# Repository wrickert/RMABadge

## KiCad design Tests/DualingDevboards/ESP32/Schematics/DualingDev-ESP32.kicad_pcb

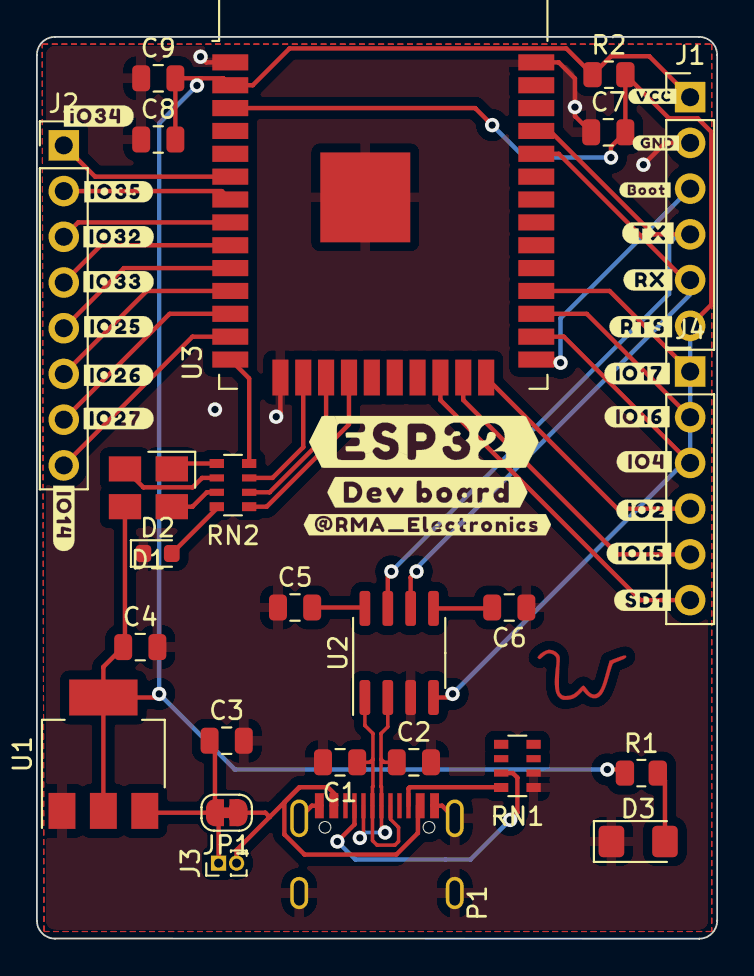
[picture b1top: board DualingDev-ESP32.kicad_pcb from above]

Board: 2 copper layers, 37.8 x 50.1 mm, 26 parts (0 on the bottom side), 37 nets.

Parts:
C1, C2: 20pF; C_0805_2012Metric
C3, C4: 1uF; C_0805_2012Metric
C5, C6, C7, C9: 100nF; C_0805_2012Metric
C8: 10uF; C_0805_2012Metric
D1: LED_BGRA; EKINGLUX-E6
D2: LED; LED_0603_1608Metric
D3: POWER; LED_1206_3216Metric_Pad1.42x1.75mm_HandSolder
J1: Program; PinHeader_1x06_P2.54mm_Vertical
J2: Conn_01x08; PinHeader_1x08_P2.54mm_Vertical
J3: Conn_01x02; PinHeader_1x02_P1.00mm_Vertical
J4: Conn_01x06; PinHeader_1x06_P2.54mm_Vertical
JP1: Jumper_NC_Small; SolderJumper-2_P1.3mm_Bridged_RoundedPad1.0x1.5mm
P1: USB_C_Plug_corrected; USB_C_Receptical-Jing
R1: R; R_0805_2012Metric
R2: 10k; R_0805_2012Metric
RN1: 5.1k; R_Array_Convex_4x0603
RN2: 270; R_Array_Convex_4x0603
Ref**: Val**; W
U1: TLV1117-33; SOT-223-3_TabPin2
U2: CH330N; SOIC-8_3.9x4.9mm_P1.27mm
U3: ESP32-WROOM-32

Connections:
1: J2.1, U3.6 (IO34)
2: J2.2, U3.7 (IO35)
3: J2.3, U3.8 (IO32)
4: J2.4, U3.9 (IO33)
5: J2.5, U3.10 (IO25)
6: J2.6, U3.11 (IO26)
7: J2.7, U3.12 (IO27)
8: J2.8, U3.13 (IO14)
/D+: C1.1, P1.A6 (D+), P1.B6 (D+), U2.1 (UD+)
/D-: C2.1, P1.A7 (D-), P1.B7 (D-), U2.2 (UD-)
A: J4.1, U3.28 (IO17)
Attention: RN2.1 (R1.1), U3.18 (SWP/SD3)
B: J4.2, U3.27 (IO16)
Blue: RN2.4 (R4.1), U3.14 (IO12)
Boot: J1.3, U3.25 (IO0)
C: J4.3, U3.26 (IO4)
D: J4.4, U3.24 (IO2)
E: J4.5, U3.23 (IO15)
F: J4.6, U3.22 (SDI/SD1)
GND: C1.2, C2.2, C3.2, C4.2, C5.1, C6.1, C7.1, C8.1, C9.1, D2.1 (K), D3.1 (K), J1.2, P1.A1 (GND), P1.A12 (GND), P1.B1 (GND), P1.B12 (GND), P1.S1 (SHIELD), RN1.1 (R1.1), RN1.2 (R2.1), U1.1 (GND), U2.3 (GND), U3.1 (GND), U3.15 (GND), U3.38 (GND), U3.39 (GND)
Green: RN2.3 (R3.1), U3.16 (IO13)
unnamed: C3.1, J3.1, JP1.2, U1.3 (VI)
unnamed: C5.2, U2.8 (V3)
unnamed: C6.2, U2.5 (VCC)
unnamed: D1.1 (BK), RN2.5 (R4.2)
unnamed: D1.2 (GK), RN2.6 (R3.2)
unnamed: D1.3 (RK), RN2.7 (R2.2)
unnamed: D2.2 (A), RN2.8 (R1.2)
unnamed: D3.2 (A), R1.2
unnamed: P1.A5 (CC), RN1.7 (R2.2)
unnamed: P1.B5 (VCONN), RN1.8 (R1.2)
RTS: C7.2, J1.6, R2.2, U2.4 (~RTS), U3.3 (EN)
RX: J1.5, U2.6 (TXD), U3.34 (RXD0/IO3)
Red: RN2.2 (R2.1), U3.17 (SHD/SD2)
TX: J1.4, U2.7 (RXD), U3.35 (TXD0/IO1)
VBUS: J3.2, JP1.1, P1.A4 (VBUS), P1.A9 (VBUS), P1.B4 (VBUS), P1.B9 (VBUS)
VCC: C4.1, C8.2, C9.2, D1.4 (A), J1.1, R1.1, R2.1, U1.2 (VO), U3.2 (VDD)

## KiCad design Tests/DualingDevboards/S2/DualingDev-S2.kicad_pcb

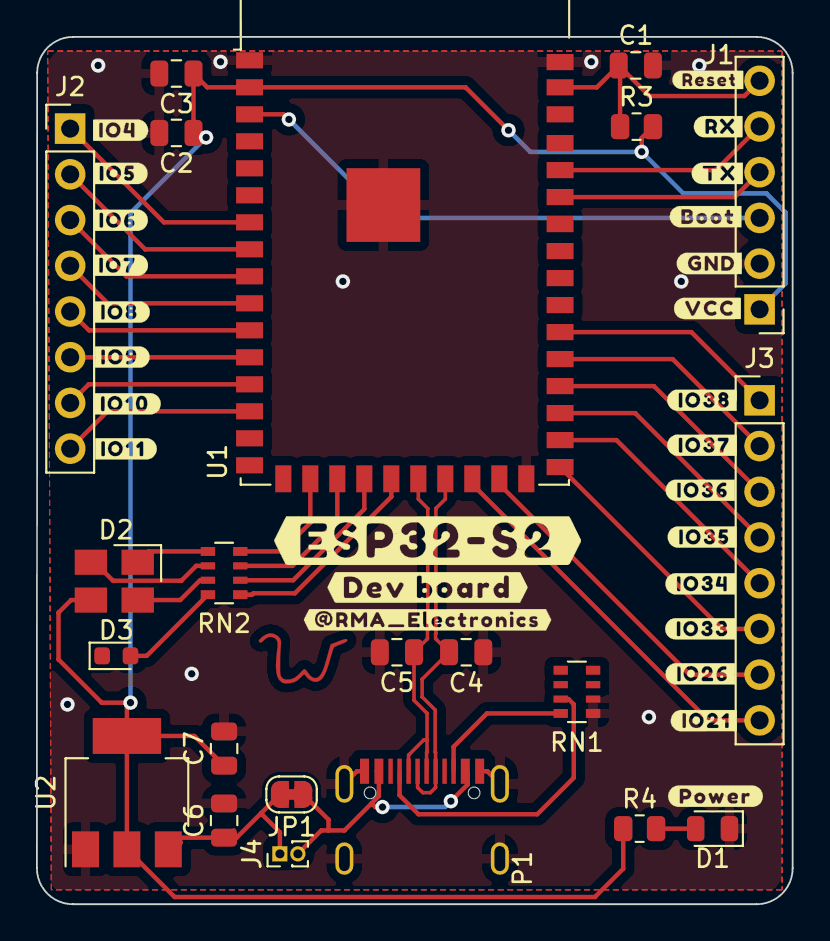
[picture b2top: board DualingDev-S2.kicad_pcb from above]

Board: 2 copper layers, 42.0 x 48.2 mm, 23 parts (0 on the bottom side), 37 nets.

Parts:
C1, C2: 100nF; C_0805_2012Metric
C3: 22uF; C_0805_2012Metric
C4, C5: 20pF; C_0805_2012Metric
C6, C7: 1uF; C_0805_2012Metric
D1: POWER; LED_0805_2012Metric
D2: LED_BGRA; EKINGLUX-E6
D3: LED; LED_0603_1608Metric
J1: Program; PinHeader_1x06_P2.54mm_Vertical
J2, J3: Conn_01x08; PinHeader_1x08_P2.54mm_Vertical
J4: Conn_01x02; PinHeader_1x02_P1.00mm_Vertical
JP1: Jumper_NC_Small; SolderJumper-2_P1.3mm_Bridged_RoundedPad1.0x1.5mm
P1: USB_C_Plug_corrected; USB_C_Receptical-Jing
R3: 1k; R_0805_2012Metric
R4: R; R_0805_2012Metric
RN1: 5.1k; R_Array_Convex_4x0603
RN2: 270; R_Array_Convex_4x0603
Ref**: Val**; W
U1: ESP32-S2-WROVER
U2: TLV1117-33; SOT-223-3_TabPin2

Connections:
/D+: C4.1, P1.A6 (D+), P1.B6 (D+), U1.23 (USB_D+)
/D-: C5.1, P1.A7 (D-), P1.B7 (D-), U1.22 (USB_D-)
Attention: RN2.1 (R1.1), U1.21 (IO18)
Blue: RN2.4 (R4.1), U1.18 (IO15)
Boot: J1.3, U1.3 (IO00)
GND: C1.2, C2.2, C3.2, C4.2, C5.2, C6.2, C7.2, D1.1 (K), J1.2, P1.A1 (GND), P1.A12 (GND), P1.B1 (GND), P1.B12 (GND), P1.S1 (SHIELD), RN1.1 (R1.1), RN1.2 (R2.1), U1.1 (GND), U1.26 (GND), U1.42 (GND), U1.43 (GND), U2.1 (GND)
Green: RN2.3 (R3.1), U1.19 (IO16)
unnamed: C6.1, J4.1, JP1.2, U2.3 (VI)
unnamed: D1.2 (A), R4.2
unnamed: D2.1 (BK), RN2.5 (R4.2)
unnamed: D2.2 (GK), RN2.6 (R3.2)
unnamed: D2.3 (RK), RN2.7 (R2.2)
unnamed: D3.2 (A), RN2.8 (R1.2)
unnamed: J2.1, U1.7 (IO04)
unnamed: J2.2, U1.8 (IO05)
unnamed: J2.3, U1.9 (IO06)
unnamed: J2.4, U1.10 (IO07)
unnamed: J2.5, U1.11 (IO08)
unnamed: J2.6, U1.12 (IO09)
unnamed: J2.7, U1.13 (IO10)
unnamed: J2.8, U1.14 (IO11)
unnamed: J3.1, U1.32 (IO38)
unnamed: J3.2, U1.31 (IO37)
unnamed: J3.3, U1.30 (IO36)
unnamed: J3.4, U1.29 (IO35)
unnamed: J3.5, U1.28 (IO34)
unnamed: J3.6, U1.27 (IO33)
unnamed: J3.7, U1.25 (IO26)
unnamed: J3.8, U1.24 (IO21)
unnamed: P1.A5 (CC), RN1.7 (R2.2)
unnamed: P1.B5 (VCONN), RN1.8 (R1.2)
RX: J1.5, U1.38 (RXD0)
Red: RN2.2 (R2.1), U1.20 (IO17)
Reset: C1.1, J1.6, R3.1, U1.41 (EN)
TX: J1.4, U1.37 (TXD0)
VBUS: J4.2, JP1.1, P1.A4 (VBUS), P1.A9 (VBUS), P1.B4 (VBUS), P1.B9 (VBUS)
VCC: C2.1, C3.1, C7.1, D2.4 (A), J1.1, R3.2, R4.1, U1.2 (3V3), U2.2 (VO)

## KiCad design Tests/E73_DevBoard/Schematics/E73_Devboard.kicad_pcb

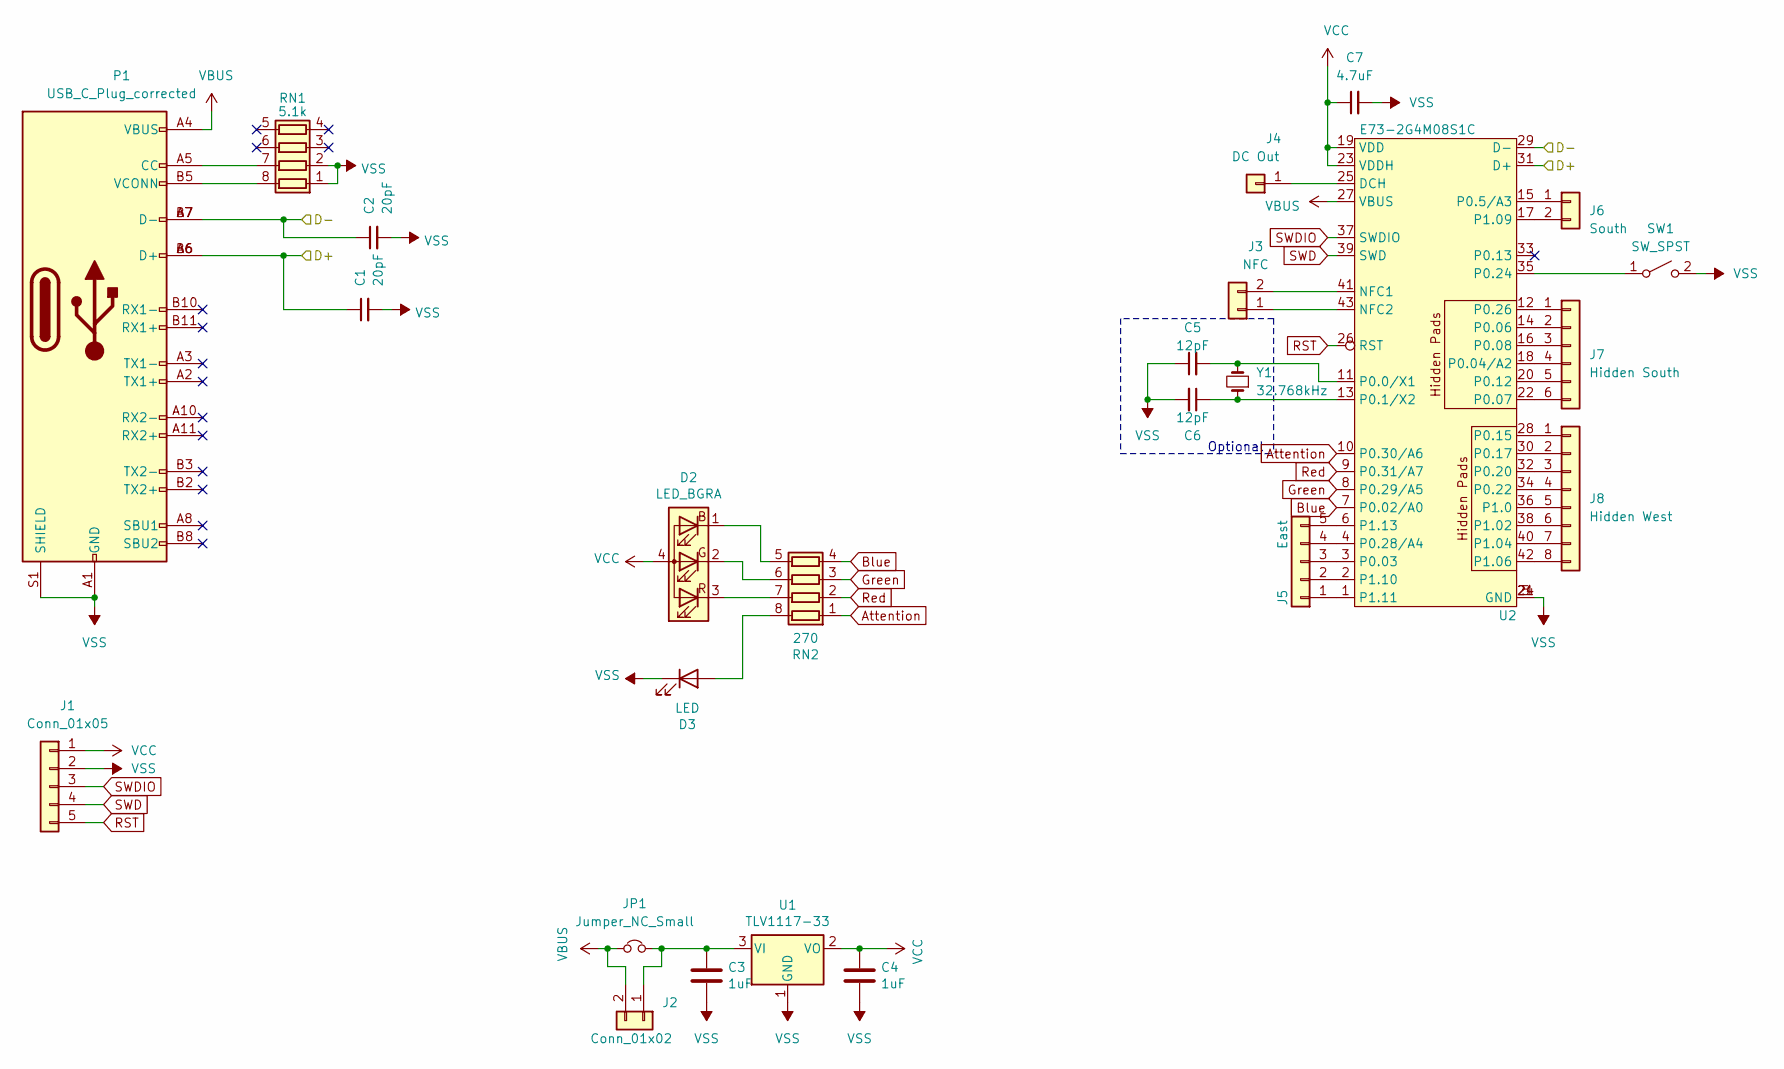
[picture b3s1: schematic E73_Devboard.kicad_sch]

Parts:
C1, C2: 20pF; C_0805_2012Metric
C3, C4: 1uF; C_0805_2012Metric
C5, C6: 12pF; C_0805_2012Metric
C7: 4.7uF; C_0805_2012Metric
D2: LED_BGRA; EKINGLUX-E6
D3: LED; LED_0603_1608Metric
J1: Conn_01x05; PinHeader_1x05_P2.54mm_Vertical
J2: Conn_01x02; PinHeader_1x02_P1.00mm_Vertical
J3: NFC; PinHeader_1x02_P2.54mm_Vertical
J4: DC Out; PinHeader_1x01_P2.54mm_Vertical
J5: East; PinHeader_1x05_P2.54mm_Vertical
J6: South; PinHeader_1x02_P2.54mm_Vertical
J7: Hidden South; PinHeader_1x06_P2.54mm_Vertical
J8: Hidden West; PinHeader_1x08_P1.00mm_Vertical_SMD_Pin1Left
JP1: Jumper_NC_Small; SolderJumper-2_P1.3mm_Bridged_RoundedPad1.0x1.5mm
P1: USB_C_Plug_corrected; USB_C_Receptical-Jing
RN1: 5.1k; R_Array_Convex_4x0603
RN2: 270; R_Array_Convex_4x0603
SW1: SW_SPST; 1TS002E-2500-2500-CT-HYP-Button
U1: TLV1117-33; SOT-223-3_TabPin2
U2: E73-2G4M08S1C
Y1: 32.768kHz; Crystal_SMD_3215-2Pin_3.2x1.5mm

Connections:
/D+: C1.1, P1.A6 (D+), P1.B6 (D+), U2.31 (D+)
/D-: C2.1, P1.A7 (D-), P1.B7 (D-), U2.29 (D-)
Attention: RN2.1 (R1.1), U2.10 (P0.30/A6)
Blue: RN2.4 (R4.1), U2.7 (P0.02/A0)
Green: RN2.3 (R3.1), U2.8 (P0.29/A5)
unnamed: C3.1, J2.1, JP1.2, U1.3 (VI)
unnamed: C5.2, U2.11 (P0.0/X1), Y1.2
unnamed: C6.1, U2.13 (P0.1/X2), Y1.1
unnamed: D2.1 (BK), RN2.5 (R4.2)
unnamed: D2.2 (GK), RN2.6 (R3.2)
unnamed: D2.3 (RK), RN2.7 (R2.2)
unnamed: D3.2 (A), RN2.8 (R1.2)
unnamed: J3.1, U2.43 (NFC2)
unnamed: J3.2, U2.41 (NFC1)
unnamed: J4.1, U2.25 (DCH)
unnamed: J5.1, U2.1 (P1.11)
unnamed: J5.2, U2.2 (P1.10)
unnamed: J5.3, U2.3 (P0.03)
unnamed: J5.4, U2.4 (P0.28/A4)
unnamed: J5.5, U2.6 (P1.13)
unnamed: J6.1, U2.15 (P0.5/A3)
unnamed: J6.2, U2.17 (P1.09)
unnamed: J7.1, U2.12 (P0.26)
unnamed: J7.2, U2.14 (P0.06)
unnamed: J7.3, U2.16 (P0.08)
unnamed: J7.4, U2.18 (P0.04/A2)
unnamed: J7.5, U2.20 (P0.12)
unnamed: J7.6, U2.22 (P0.07)
unnamed: J8.1, U2.28 (P0.15)
unnamed: J8.2, U2.30 (P0.17)
unnamed: J8.3, U2.32 (P0.20)
unnamed: J8.4, U2.34 (P0.22)
unnamed: J8.5, U2.36 (P1.0)
unnamed: J8.6, U2.38 (P1.02)
unnamed: J8.7, U2.40 (P1.04)
unnamed: J8.8, U2.42 (P1.06)
unnamed: P1.A5 (CC), RN1.7 (R2.2)
unnamed: P1.B5 (VCONN), RN1.8 (R1.2)
unnamed: SW1.1 (A), U2.35 (P0.24)
RST: J1.5, U2.26 (RST)
Red: RN2.2 (R2.1), U2.9 (P0.31/A7)
SWD: J1.4, U2.39 (SWD)
SWDIO: J1.3, U2.37 (SWDIO)
VBUS: J2.2, JP1.1, P1.A4 (VBUS), P1.A9 (VBUS), P1.B4 (VBUS), P1.B9 (VBUS), U2.27 (VBUS)
VCC: C4.1, C7.1, D2.4 (A), J1.1, U1.2 (VO), U2.19 (VDD), U2.23 (VDDH)
VSS: C1.2, C2.2, C3.2, C4.2, C5.1, C6.2, C7.2, D3.1 (K), J1.2, P1.A1 (GND), P1.A12 (GND), P1.B1 (GND), P1.B12 (GND), P1.S1 (SHIELD), RN1.1 (R1.1), RN1.2 (R2.1), SW1.2 (B), U1.1 (GND), U2.5 (GND), U2.21 (GND), U2.24 (GND)

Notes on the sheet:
Optional

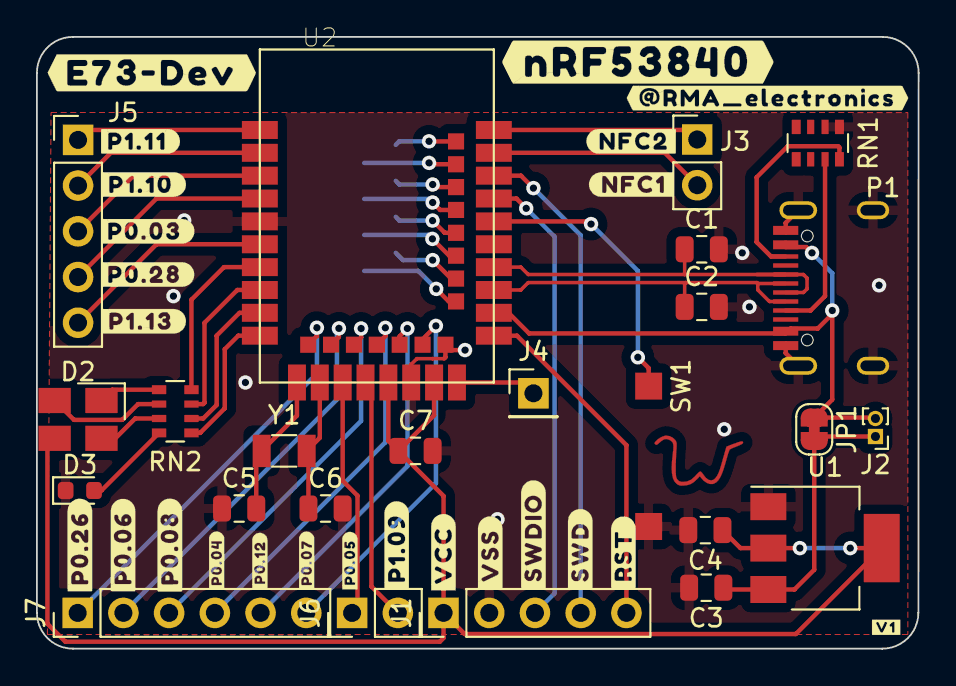
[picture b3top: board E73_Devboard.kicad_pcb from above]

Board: 2 copper layers, 49.0 x 34.0 mm, 26 parts (1 on the bottom side), 46 nets.

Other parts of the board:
Ref**: Val**; W

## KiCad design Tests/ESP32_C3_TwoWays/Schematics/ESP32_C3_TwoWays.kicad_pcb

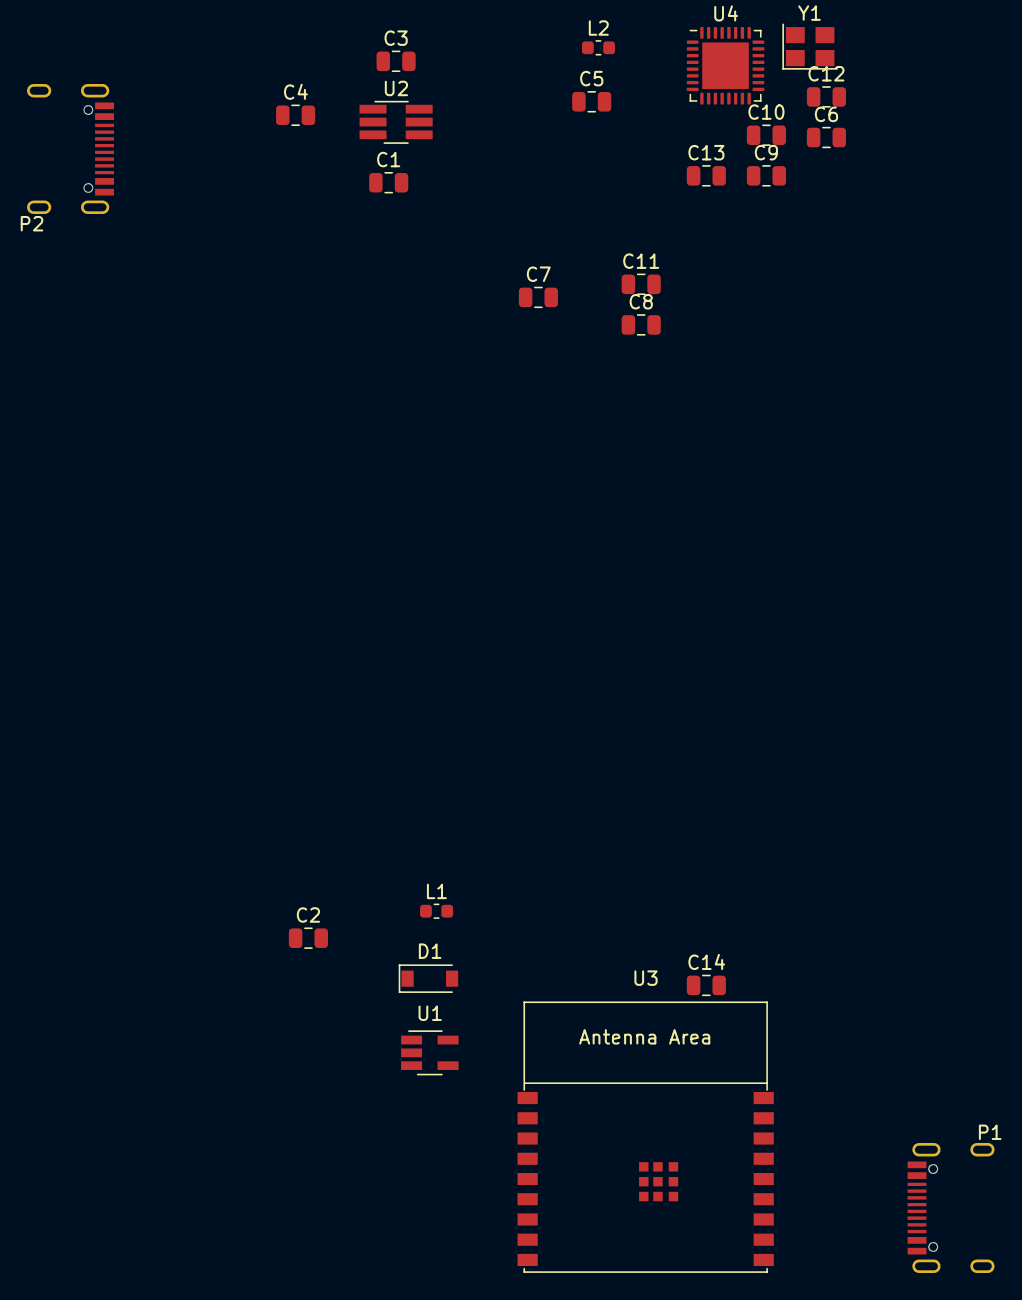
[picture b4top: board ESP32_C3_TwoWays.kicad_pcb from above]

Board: 2 copper layers, 24 parts (0 on the bottom side), 15 nets, no tracks yet.

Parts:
C1, C4, C6: 10uF; C_0805_2012Metric
C2: 47uF; C_0805_2012Metric
C3: 2.2uF; C_0805_2012Metric
C5, C8, C14: C_Small; C_0805_2012Metric
C7: 1uF; C_0805_2012Metric
C9, C10, C12, C13: 100nF; C_0805_2012Metric
C11: 10nF; C_0805_2012Metric
D1: Schottky; D_SOD-123
L1: L_Small; L_0603_1608Metric
L2: 2nH; L_0603_1608Metric
P1, P2: USB_C_Plug; USB_C_Receptical-Jing
U1: RN5RK331A; SOT-23-5_HandSoldering
U2: XDS_TX4310B; TSOT-23-6_HandSoldering
U3: ESP32-C3-WROOM-02
U4: ESP32-C3; QFN-32-1EP_5x5mm_P0.5mm_EP3.45x3.45mm
Y1: 40MHz; Crystal_SMD_3225-4Pin_3.2x2.5mm

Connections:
+5V: L1.1, P1.A4 (VBUS), P1.A9 (VBUS), P1.B4 (VBUS), P1.B9 (VBUS)
D1+: P2.A6 (D+), U4.26 (GPIO19/USB_D+)
D1-: P2.A7 (D-), U4.25 (GPIO18/USB_D-)
D2+: P1.A6 (D+), U3.14 (GPIO19/USB_D+)
D2-: P1.A7 (D-), U3.13 (GPIO18/USB_D-)
unnamed: C3.1, U2.6 (C+)
unnamed: C3.2, U2.4 (C-)
unnamed: C5.2, U4.30 (XTAL_P), Y1.1
unnamed: C8.2, U4.29 (XTAL_N), Y1.3
unnamed: C12.1, L2.2, U4.2 (VDD3P3), U4.3 (VDD3P3)
unnamed: D1.2 (A), L1.2, U1.5 (Lx)
VAA: C2.2, C14.1, D1.1 (K), U1.1 (En), U1.2 (Vout), U3.1 (3V3)
VBUS: C1.1, P2.A4 (VBUS), P2.A9 (VBUS), P2.B4 (VBUS), P2.B9 (VBUS), U2.3 (En), U2.5 (VDD)
VCC: C4.1, C6.1, C7.1, C9.1, C10.1, C11.1, C13.1, L2.1, U2.1 (Vout), U4.11 (VDD3P3_RTC), U4.17 (VDD3P3_CPU), U4.31 (VDDA), U4.32 (VDDA)
VSS: C1.2, C2.1, C4.2, C5.1, C6.2, C7.2, C8.1, C9.2, C10.2, C11.2, C12.2, C13.2, C14.2, P1.A1 (GND), P1.A12 (GND), P1.B1 (GND), P1.B12 (GND), P1.S1 (SHIELD), P2.A1 (GND), P2.A12 (GND), P2.B1 (GND), P2.B12 (GND), P2.S1 (SHIELD), U1.4 (GND), U2.2 (GND), U3.9 (GND), U3.19 (GND), U4.33 (GND), Y1.2, Y1.4

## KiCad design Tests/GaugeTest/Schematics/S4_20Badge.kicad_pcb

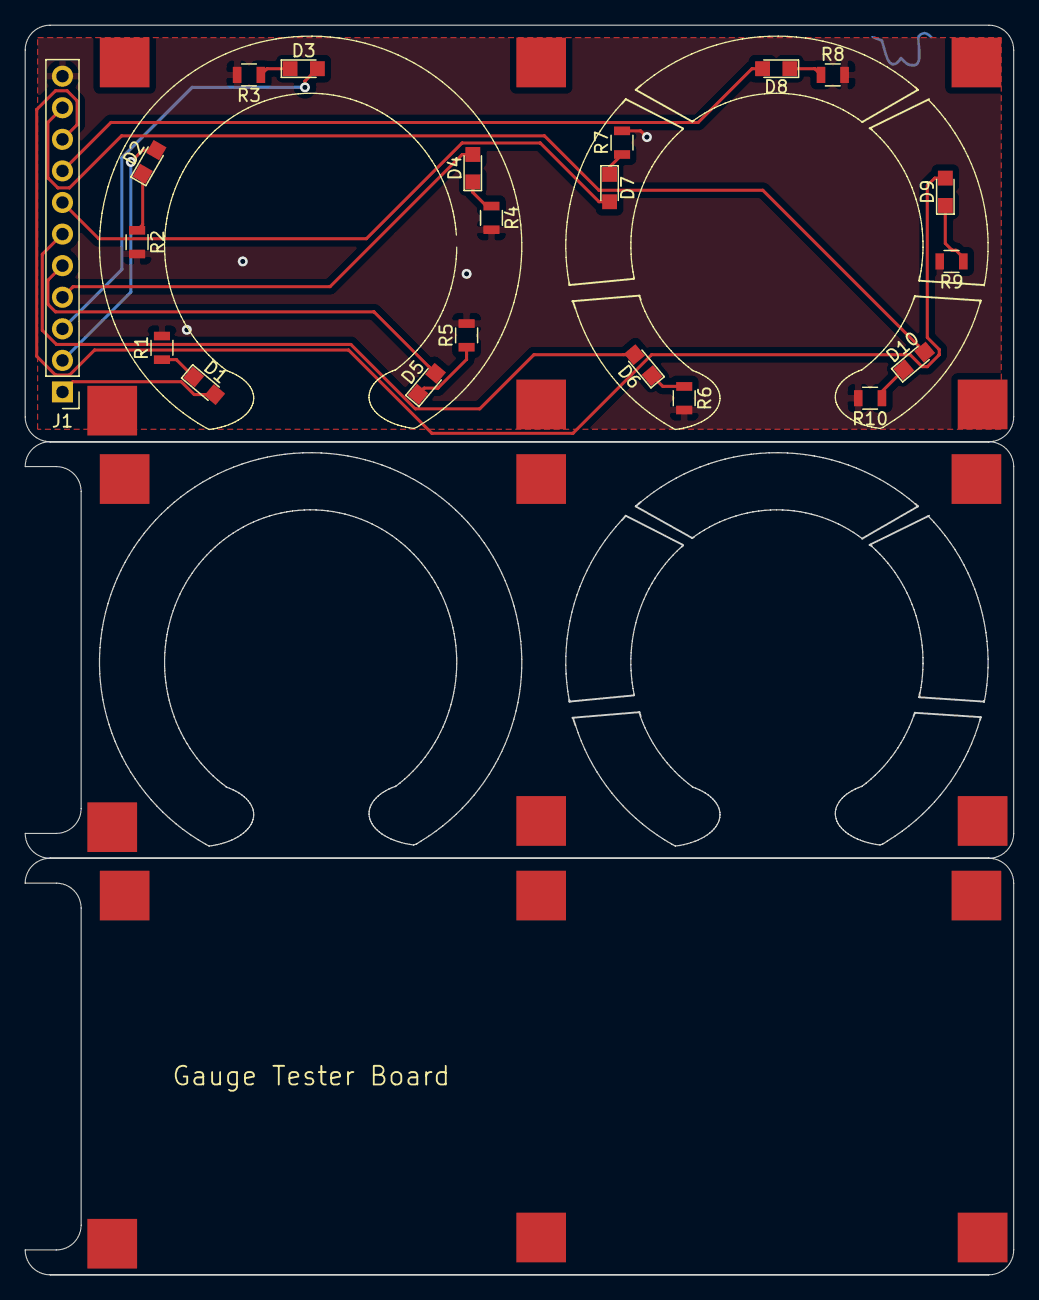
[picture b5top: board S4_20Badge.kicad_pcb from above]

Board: 2 copper layers, 79.5 x 100.5 mm, 27 parts (1 on the bottom side), 21 nets.

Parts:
D1, D2, D3, D4, D5, D6, D7, D8, D9, D10: LED; LED_0805
J1: Conn_01x11; Pin_Header_Straight_1x11_Pitch2.54mm
R1, R2, R3, R4, R5, R6, R7, R8, R9, R10: R_Small; R_0805
Ref**: Val**; W
Ref**#2: Val**; Gauge_silk
Ref**#3: Val**; Gauge_Open_Silk
Ref**#4: Val**; Gauge_Open_mask
Ref**#5, Ref**#6: Val**; Gauge

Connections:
unnamed: D1.1, R1.1
unnamed: D2.1, R2.1
unnamed: D3.1, R3.1
unnamed: D4.1, R4.1
unnamed: D5.1, R5.1
unnamed: D6.1, R6.1
unnamed: D7.1, R7.1
unnamed: D8.1, R8.1
unnamed: D9.1, R9.1
unnamed: D10.1, R10.1
VSS: J1.11, R1.2, R2.2, R3.2, R4.2, R5.2, R6.2, R7.2, R8.2, R9.2, R10.2
a: D1.2, J1.1
b: D2.2, J1.2
c: D3.2, J1.3
d: D4.2, J1.4
e: D5.2, J1.5
f: D6.2, J1.6
g: D7.2, J1.7
h: D8.2, J1.8
i: D9.2, J1.9
j: D10.2, J1.10

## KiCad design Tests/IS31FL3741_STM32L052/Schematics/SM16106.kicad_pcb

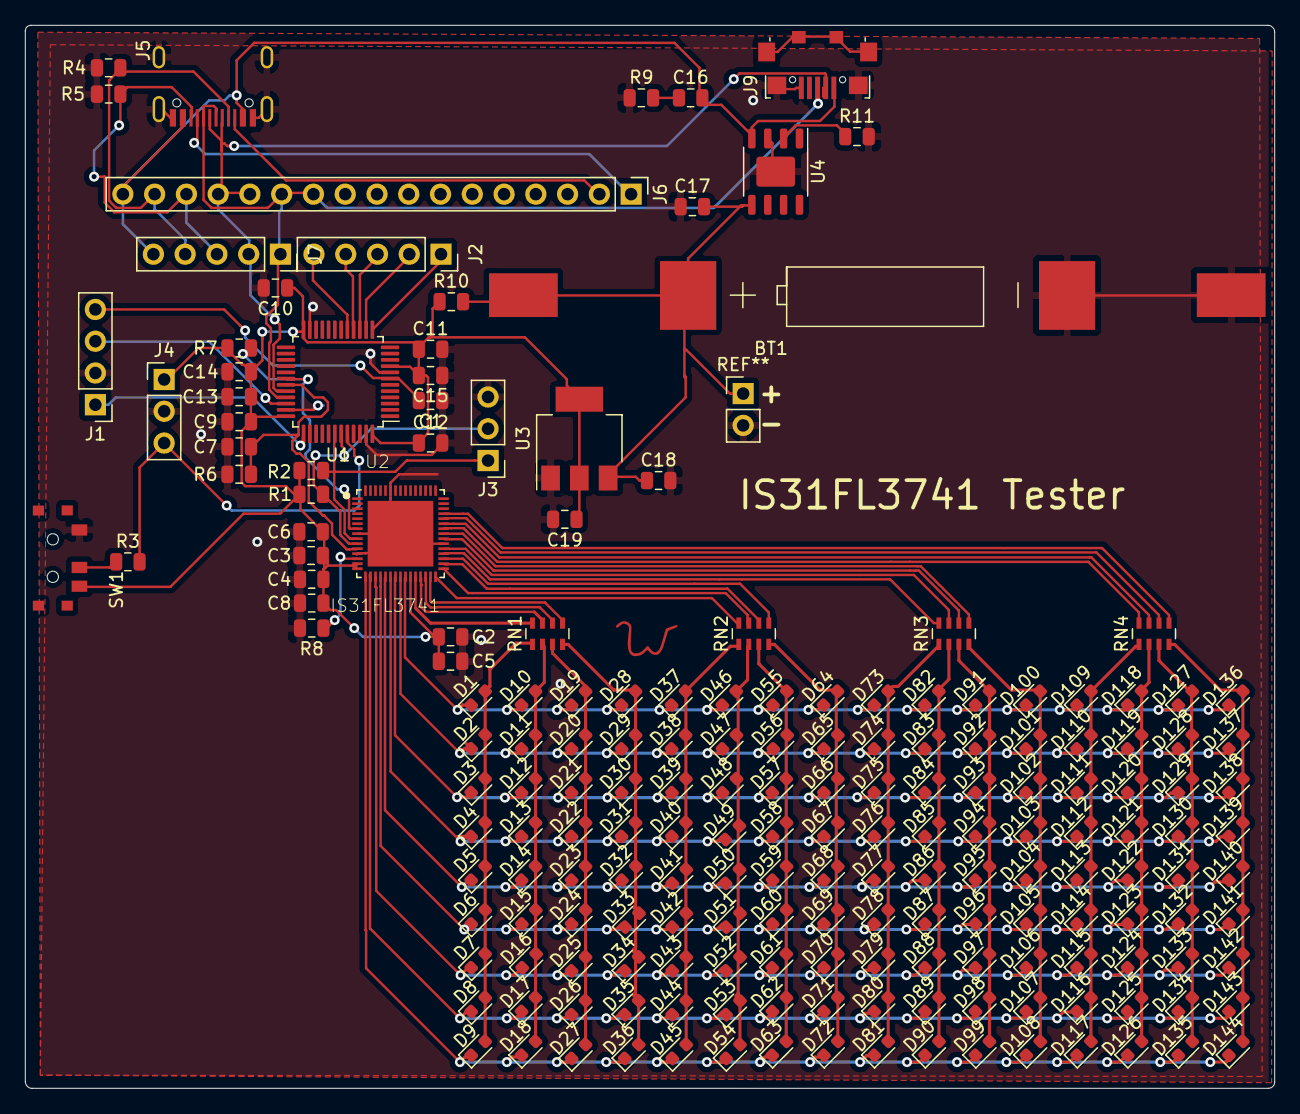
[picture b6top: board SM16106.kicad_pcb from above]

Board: 2 copper layers, 99.9 x 85.0 mm, 193 parts (0 on the bottom side), 68 nets.

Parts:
BT1: Battery_Cell; Dongguan14500
C1, C9, C10, C11, C12, C13: 100nF; C_0805_2012Metric
C2, C3, C4, C15, C18, C19: 1uF; C_0805_2012Metric
C5, C6, C7, C8: 100pF; C_0805_2012Metric
C14, C16, C17: 10uF; C_0805_2012Metric
D1, D2, D3, D4, D5, D6, D7, D8, D9, D10, D11, D12, D13, D14, D15, D16, D17, D18, D19, D20, D21, D22, D23, D24, D25, D26, D27, D28, D29, D30, D31, D32, D33, D34, D35, D36, D37, D38, D39, D40, D41, D42, D43, D44, D45, D46, D47, D48, D49, D50, D51, D52, D53, D54, D55, D56, D57, D58, D59, D60, D61, D62, D63, D64, D65, D66, D67, D68, D69, D70, D71, D72, D73, D74, D75, D76, D77, D78, D79, D80, D81, D82, D83, D84, D85, D86, D87, D88, D89, D90, D91, D92, D93, D94, D95, D96, D97, D98, D99, D100, D101, D102, D103, D104, D105, D106, D107, D108, D109, D110, D111, D112, D113, D114, D115, D116, D117, D118, D119, D120, D121, D122, D123, D124, D125, D126, D127, D128, D129, D130, D131, D132, D133, D134, D135, D136, D137, D138, D139, D140, D141, D142, D143, D144: LED; LED_0603_1608Metric
J1: Prog; PinHeader_1x04_P2.54mm_Vertical
J2: Expansion; PinSocket_1x05_P2.54mm_Vertical
J3: i2c; PinHeader_1x03_P2.54mm_Vertical
J4: Conn_01x03; PinHeader_1x03_P2.54mm_Vertical
J5: USB_C_Receptacle; USB_C_Receptical-Jing
J6: Conn_01x17; PinHeader_1x17_P2.54mm_Vertical
J7: Conn_01x05; PinSocket_1x05_P2.54mm_Vertical
J9: USB_B_Micro; USB_Micro-B_Jing
R1, R2: 2k; R_0805_2012Metric
R3, R4, R5, R6, R7, R8: 10k; R_0805_2012Metric
R9: 1.5; R_0805_2012Metric
R10: 0ohm; R_0805_2012Metric
R11: 1k; R_0805_2012Metric
RN1, RN2, RN3, RN4: R_Pack04; R_Array_Concave_4x0603
Ref**: Val**; W
SW1: SW_SPDT; SK-3296S_switch
U1: STM32L052C8Tx; LQFP-48_7x7mm_P0.5mm
U2: IS31FL3741; QFN40P700X700X75-61N
U3: TLV1117-33; SOT-223-3_TabPin2
U4: HX4056; HSOP-8-1EP_3.9x4.9mm_P1.27mm_EP2.41x3.1mm

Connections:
+5V: C16.2, J5.A4, J5.A9, J5.B4, J5.B9, J6.17, J7.5, J9.1, U4.4
/INTB: R7.1, U1.30, U2.7
/SCL: J3.1, R2.2, U1.42, U2.9
/SDA: J3.2, R1.2, U1.43, U2.10
/SDB: C7.1, R6.2, U1.31, U2.11
Boot0: J4.3, R3.2, U1.44
C1: D1.2, D2.2, D3.2, D4.2, D5.2, D6.2, D7.2, D8.2, D9.2, RN1.1
C2: D10.2, D11.2, D12.2, D13.2, D14.2, D15.2, D16.2, D17.2, D18.2, RN1.2
C3: D19.2, D20.2, D21.2, D22.2, D23.2, D24.2, D25.2, D26.2, D27.2, RN1.3
C4: D28.2, D29.2, D30.2, D31.2, D32.2, D33.2, D34.2, D35.2, D36.2, RN1.4
C5: D37.2, D38.2, D39.2, D40.2, D41.2, D42.2, D43.2, D44.2, D45.2, RN2.1
C6: D46.2, D47.2, D48.2, D49.2, D50.2, D51.2, D52.2, D53.2, D54.2, RN2.2
C7: D55.2, D56.2, D57.2, D58.2, D59.2, D60.2, D61.2, D62.2, D63.2, RN2.3
C8: D64.2, D65.2, D66.2, D67.2, D68.2, D69.2, D70.2, D71.2, D72.2, RN2.4
C9: D73.2, D74.2, D75.2, D76.2, D77.2, D78.2, D79.2, D80.2, D81.2, RN3.1
C10: D82.2, D83.2, D84.2, D85.2, D86.2, D87.2, D88.2, D89.2, D90.2, RN3.2
C11: D91.2, D92.2, D93.2, D94.2, D95.2, D96.2, D97.2, D98.2, D99.2, RN3.3
C12: D100.2, D101.2, D102.2, D103.2, D104.2, D105.2, D106.2, D107.2, D108.2, RN3.4
C13: D109.2, D110.2, D111.2, D112.2, D113.2, D114.2, D115.2, D116.2, D117.2, RN4.1
C14: D118.2, D119.2, D120.2, D121.2, D122.2, D123.2, D124.2, D125.2, D126.2, RN4.2
C15: D127.2, D128.2, D129.2, D130.2, D131.2, D132.2, D133.2, D134.2, D135.2, RN4.3
C16: D136.2, D137.2, D138.2, D139.2, D140.2, D141.2, D142.2, D143.2, D144.2, RN4.4
D+: J5.A6, J5.B6, J6.11, J6.12, J7.1, J9.3, U1.33
D-: J5.A7, J5.B7, J6.13, J6.14, J7.2, J9.2, U1.32
GND: BT1.2, C1.1, C2.2, C3.2, C4.2, C5.2, C6.2, C7.2, C8.2, C9.2, C10.2, C11.2, C12.2, C13.2, C14.2, C15.2, C17.1, C18.2, C19.2, J1.2, J3.3, J4.2, J5.A1, J5.A12, J5.B1, J5.B12, J5.S1, J9.5, J9.6, R4.1, R5.1, R6.1, R8.2, R9.1, R11.2, SW1.3, U1.8, U1.23, U1.35, U1.47, U2.8, U2.12, U2.36, U2.55, U2.61, U3.1, U4.3, U4.9
unnamed: C16.1, R9.2
unnamed: J5.A5, J6.16, J7.4, R4.2
unnamed: J5.A8, J6.2
unnamed: J5.B5, J6.15, J7.3, R5.2
unnamed: J5.B8, J6.1
unnamed: R3.1, SW1.2
unnamed: R8.1, U2.13
unnamed: R11.1, U4.2
unnamed: RN1.5, U2.29
unnamed: RN1.6, U2.28
unnamed: RN1.7, U2.27
unnamed: RN1.8, U2.26
unnamed: RN2.5, U2.33
unnamed: RN2.6, U2.32
unnamed: RN2.7, U2.31
unnamed: RN2.8, U2.30
unnamed: RN3.5, U2.38
unnamed: RN3.6, U2.37
unnamed: RN3.7, U2.35
unnamed: RN3.8, U2.34
unnamed: RN4.5, U2.42
unnamed: RN4.6, U2.41
unnamed: RN4.7, U2.40
unnamed: RN4.8, U2.39
PA3: J2.1, U1.13
PA4: J2.2, U1.14
PA5: J2.3, U1.15
PA6: J2.4, U1.16
PA7: J2.5, U1.17
R1: D1.1, D10.1, D19.1, D28.1, D37.1, D46.1, D55.1, D64.1, D73.1, D82.1, D91.1, D100.1, D109.1, D118.1, D127.1, D136.1, U2.24
R2: D2.1, D11.1, D20.1, D29.1, D38.1, D47.1, D56.1, D65.1, D74.1, D83.1, D92.1, D101.1, D110.1, D119.1, D128.1, D137.1, U2.23
R3: D3.1, D12.1, D21.1, D30.1, D39.1, D48.1, D57.1, D66.1, D75.1, D84.1, D93.1, D102.1, D111.1, D120.1, D129.1, D138.1, U2.22
R4: D4.1, D13.1, D22.1, D31.1, D40.1, D49.1, D58.1, D67.1, D76.1, D85.1, D94.1, D103.1, D112.1, D121.1, D130.1, D139.1, U2.21
R5: D5.1, D14.1, D23.1, D32.1, D41.1, D50.1, D59.1, D68.1, D77.1, D86.1, D95.1, D104.1, D113.1, D122.1, D131.1, D140.1, U2.20
R6: D6.1, D15.1, D24.1, D33.1, D42.1, D51.1, D60.1, D69.1, D78.1, D87.1, D96.1, D105.1, D114.1, D123.1, D132.1, D141.1, U2.19
R7: D7.1, D16.1, D25.1, D34.1, D43.1, D52.1, D61.1, D70.1, D79.1, D88.1, D97.1, D106.1, D115.1, D124.1, D133.1, D142.1, U2.18
R8: D8.1, D17.1, D26.1, D35.1, D44.1, D53.1, D62.1, D71.1, D80.1, D89.1, D98.1, D107.1, D116.1, D125.1, D134.1, D143.1, U2.17
R9: D9.1, D18.1, D27.1, D36.1, D45.1, D54.1, D63.1, D72.1, D81.1, D90.1, D99.1, D108.1, D117.1, D126.1, D135.1, D144.1, U2.16
Reset: C1.2, J1.4, U1.7
SWCLK: J1.1, U1.37
SWDIO: J1.3, U1.34
VCC: C2.1, C3.1, C4.1, C5.1, C6.1, C8.1, C9.1, C10.1, C11.1, C12.1, C13.1, C14.1, C15.1, C19.1, J4.1, R1.1, R2.1, R7.2, SW1.1, U1.9, U1.24, U1.36, U1.48, U2.14, U2.15, U2.25, U3.2
VDDA: BT1.1, C17.2, C18.1, R10.2, U3.3, U4.5

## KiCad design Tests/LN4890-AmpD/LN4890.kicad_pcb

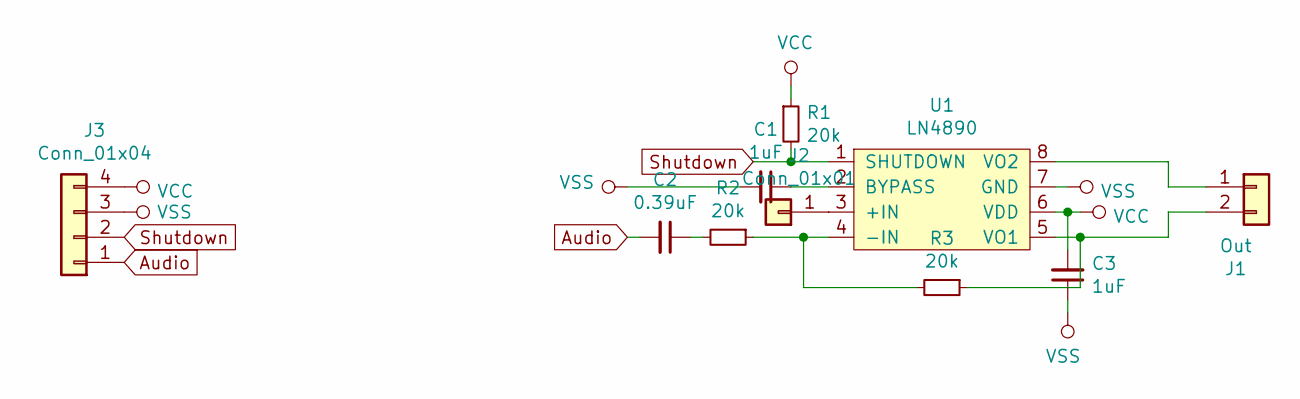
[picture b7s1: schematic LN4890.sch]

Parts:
C1, C3: 1uF; C_0805_2012Metric
C2: 0.39uF; C_0805_2012Metric
J1: Out; TerminalBlock_Altech_AK300-2_P5.00mm
J2: Conn_01x01; PinHeader_1x01_P2.54mm_Vertical
J3: Conn_01x04; PinHeader_1x04_P2.54mm_Vertical
R1, R2, R3: 20k; R_0805_2012Metric
U1: LN4890; TSSOP-8_3x3mm_P0.65mm

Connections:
Audio: C2.2, J3.1
unnamed: C1.1, U1.2 (BYPASS)
unnamed: C2.1, R2.2
unnamed: J1.1, U1.8 (VO2)
unnamed: J1.2, R3.1, U1.5 (VO1)
unnamed: J2.1, U1.3 (+IN)
unnamed: R2.1, R3.2, U1.4 (-IN)
Shutdown: J3.2, R1.2, U1.1 (SHUTDOWN)
VCC: C3.2, J3.4, R1.1, U1.6 (VDD)
VSS: C1.2, C3.1, J3.3, U1.7 (GND)

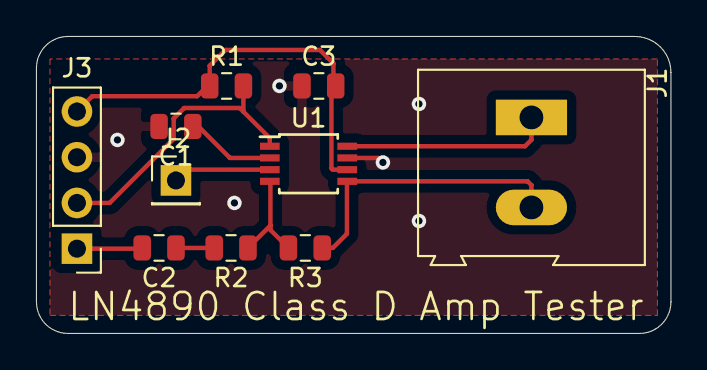
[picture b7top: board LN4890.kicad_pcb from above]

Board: 2 copper layers, 35.2 x 16.5 mm, 10 parts (0 on the bottom side), 10 nets.

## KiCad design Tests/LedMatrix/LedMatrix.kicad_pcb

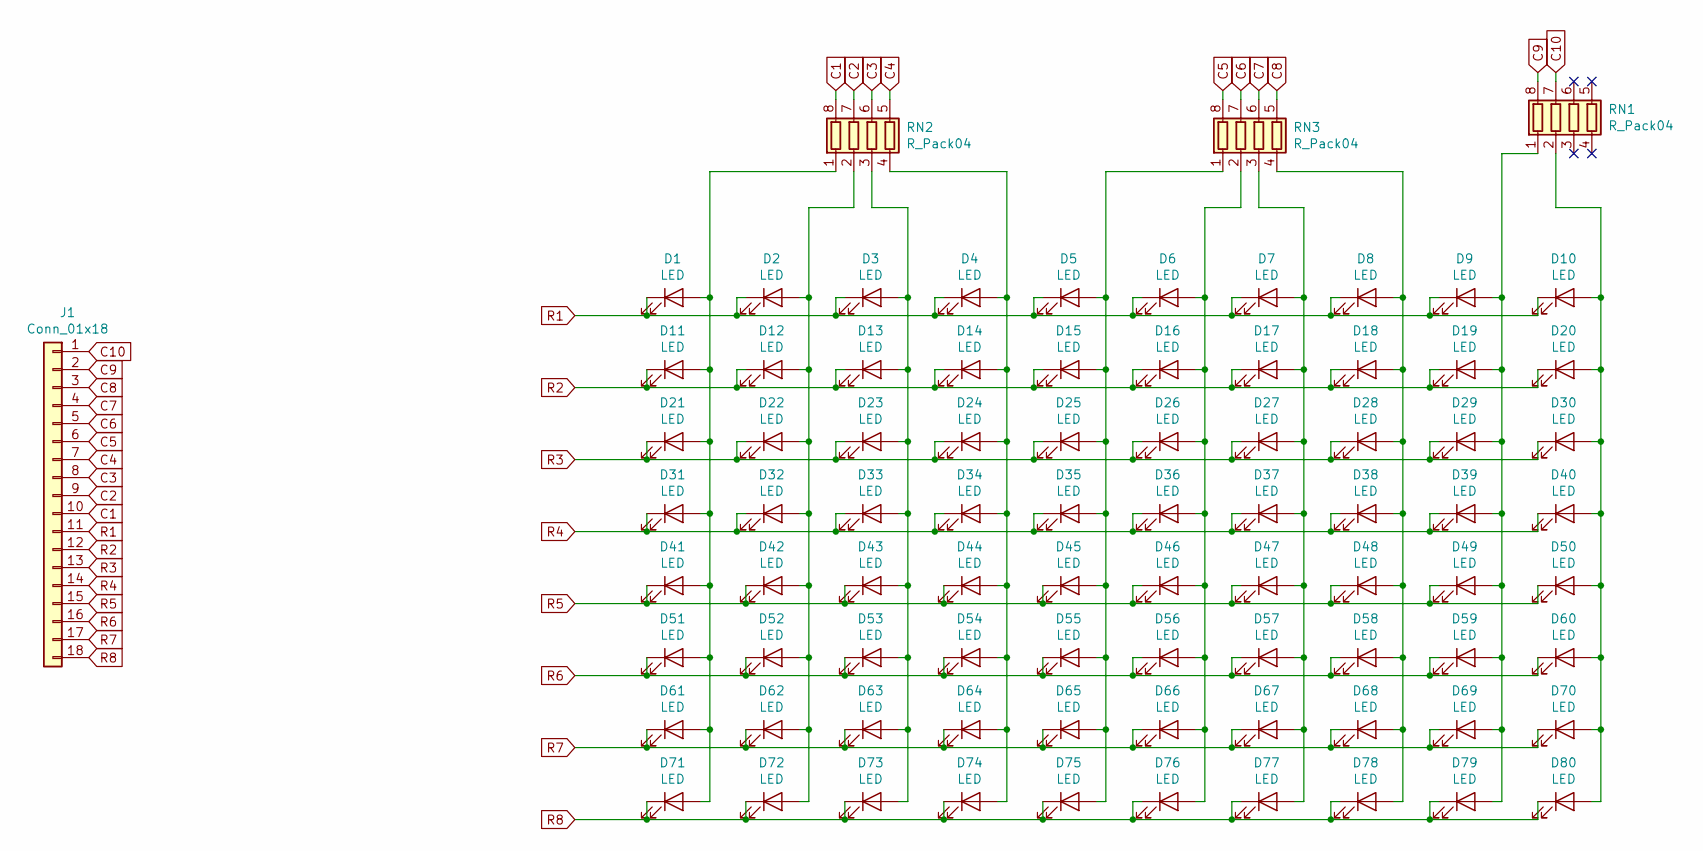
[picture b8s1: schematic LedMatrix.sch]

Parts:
D1, D2, D3, D4, D5, D6, D7, D8, D9, D10, D11, D12, D13, D14, D15, D16, D17, D18, D19, D20, D21, D22, D23, D24, D25, D26, D27, D28, D29, D30, D31, D32, D33, D34, D35, D36, D37, D38, D39, D40, D41, D42, D43, D44, D45, D46, D47, D48, D49, D50, D51, D52, D53, D54, D55, D56, D57, D58, D59, D60, D61, D62, D63, D64, D65, D66, D67, D68, D69, D70, D71, D72, D73, D74, D75, D76, D77, D78, D79, D80: LED; LED_0603
J1: Conn_01x18; Pin_Header_Straight_1x18_Pitch2.54mm
RN1, RN2, RN3: R_Pack04; R_Array_Concave_4x0603

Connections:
C1: J1.10, RN2.8 (R1.2)
C2: J1.9, RN2.7 (R2.2)
C3: J1.8, RN2.6 (R3.2)
C4: J1.7, RN2.5 (R4.2)
C5: J1.6, RN3.8 (R1.2)
C6: J1.5, RN3.7 (R2.2)
C7: J1.4, RN3.6 (R3.2)
C8: J1.3, RN3.5 (R4.2)
C9: J1.2, RN1.8 (R1.2)
C10: J1.1, RN1.7 (R2.2)
unnamed: D1.2 (A), D11.2 (A), D21.2 (A), D31.2 (A), D41.2 (A), D51.2 (A), D61.2 (A), D71.2 (A), RN2.1 (R1.1)
unnamed: D10.2 (A), D20.2 (A), D30.2 (A), D40.2 (A), D50.2 (A), D60.2 (A), D70.2 (A), D80.2 (A), RN1.2 (R2.1)
unnamed: D2.2 (A), D12.2 (A), D22.2 (A), D32.2 (A), D42.2 (A), D52.2 (A), D62.2 (A), D72.2 (A), RN2.2 (R2.1)
unnamed: D3.2 (A), D13.2 (A), D23.2 (A), D33.2 (A), D43.2 (A), D53.2 (A), D63.2 (A), D73.2 (A), RN2.3 (R3.1)
unnamed: D4.2 (A), D14.2 (A), D24.2 (A), D34.2 (A), D44.2 (A), D54.2 (A), D64.2 (A), D74.2 (A), RN2.4 (R4.1)
unnamed: D5.2 (A), D15.2 (A), D25.2 (A), D35.2 (A), D45.2 (A), D55.2 (A), D65.2 (A), D75.2 (A), RN3.1 (R1.1)
unnamed: D6.2 (A), D16.2 (A), D26.2 (A), D36.2 (A), D46.2 (A), D56.2 (A), D66.2 (A), D76.2 (A), RN3.2 (R2.1)
unnamed: D7.2 (A), D17.2 (A), D27.2 (A), D37.2 (A), D47.2 (A), D57.2 (A), D67.2 (A), D77.2 (A), RN3.3 (R3.1)
unnamed: D8.2 (A), D18.2 (A), D28.2 (A), D38.2 (A), D48.2 (A), D58.2 (A), D68.2 (A), D78.2 (A), RN3.4 (R4.1)
unnamed: D9.2 (A), D19.2 (A), D29.2 (A), D39.2 (A), D49.2 (A), D59.2 (A), D69.2 (A), D79.2 (A), RN1.1 (R1.1)
R1: D1.1 (K), D2.1 (K), D3.1 (K), D4.1 (K), D5.1 (K), D6.1 (K), D7.1 (K), D8.1 (K), D9.1 (K), D10.1 (K), J1.11
R2: D11.1 (K), D12.1 (K), D13.1 (K), D14.1 (K), D15.1 (K), D16.1 (K), D17.1 (K), D18.1 (K), D19.1 (K), D20.1 (K), J1.12
R3: D21.1 (K), D22.1 (K), D23.1 (K), D24.1 (K), D25.1 (K), D26.1 (K), D27.1 (K), D28.1 (K), D29.1 (K), D30.1 (K), J1.13
R4: D31.1 (K), D32.1 (K), D33.1 (K), D34.1 (K), D35.1 (K), D36.1 (K), D37.1 (K), D38.1 (K), D39.1 (K), D40.1 (K), J1.14
R5: D41.1 (K), D42.1 (K), D43.1 (K), D44.1 (K), D45.1 (K), D46.1 (K), D47.1 (K), D48.1 (K), D49.1 (K), D50.1 (K), J1.15
R6: D51.1 (K), D52.1 (K), D53.1 (K), D54.1 (K), D55.1 (K), D56.1 (K), D57.1 (K), D58.1 (K), D59.1 (K), D60.1 (K), J1.16
R7: D61.1 (K), D62.1 (K), D63.1 (K), D64.1 (K), D65.1 (K), D66.1 (K), D67.1 (K), D68.1 (K), D69.1 (K), D70.1 (K), J1.17
R8: D71.1 (K), D72.1 (K), D73.1 (K), D74.1 (K), D75.1 (K), D76.1 (K), D77.1 (K), D78.1 (K), D79.1 (K), D80.1 (K), J1.18
